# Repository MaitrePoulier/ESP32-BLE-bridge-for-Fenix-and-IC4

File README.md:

# ESP32 BaseBoard - IC4 Bridge

**IC4 Bridge** turns the ESP32 BaseBoard into a Bluetooth bridge for indoor cycling. A Garmin Fenix 8 no longer
connects to the Schwinn IC4 bike (Garmin bug in FTMS "Trainer" mode). The bridge connects to the bike instead and
sends its data again as a standard **cycling power sensor** that the watch accepts: power, cadence, speed and
distance. It also reads the heart rate of a **Garmin HRM 600** strap.

On its 4" screen, next to the bike:

* at the top, the state of each link (IC4, Fenix, HRM 600) with a coloured dot, and the time of day;
* on the left, the heart rate in a gauge coloured by heart rate zone, with the current zone below;
* in the centre, the power (W) and the distance of the session (km);
* on the right, the cadence in a gauge coloured by cadence zone (green: target cadence).

Touching the screen shows a diagnostic page for the IC4 link.

## BaseBoard

* 2x 18650 LiFePo4 cells that can be charged with the USB connector: more than 5 h of use as an IC4 Bridge
* Low noise +/- 12.4 V going to the mezzanine to power the audio op-amps
* I2S port going to the mezzanine
* MHS 4.0" screen (ST7796S, 480 x 320) with touch (XPT2046)
* Fits inside a Pelican 1040 Micro Case

The IC4 Bridge uses no mezzanine (no audio): the +/- 12.4 V and the I2S port are unused.

The board is easy to order assembled from JLCPCB: the LCSC part numbers are in the schematic, and the production
files (Gerber, BOM, CPL) are in `Hardware/jlcpcb/production_files/` (JLCPCB Tools plugin for KiCad).

Folders: `Hardware/` (KiCad), `Enclosure/` (3D models of the case), `Datasheets/`, `Design/` (pictures of the
README, design notes), `Firmware/`.

## Firmware

ESP-IDF v6.1 project (ESP32-WROOM-32E-N8R2), NimBLE, LVGL 9 for the GUI.

```bash
cd Firmware
idf.py set-target esp32      # only the first time
idf.py build
idf.py -p /dev/ttyUSB0 flash monitor
```

* `main/` : application sources, `main/include/` : headers
* `main/include/Config.h` : pins of the board (screen, touch, I2S, battery), bridge constants, heart rate and
  cadence zones
* `sdkconfig.defaults` : project configuration (PSRAM, flash 8 MB, LVGL and its fonts, NimBLE, watchdog, core dump)
* `main/idf_component.yml` : external components (LVGL), downloaded in `managed_components/`

Serial console (115200 bauds, ANSI terminal such as Tera Term or `idf.py monitor`; opening the port resets the
board): type `help`.

* `bridge` (status of the links, last FTMS frame decoded, data sent), `bridge raw [off]` (every frame),
  `bridge log [clear]` (event log), `bridge unpair` (erase the bonds kept by the bridge)
* `hrm` (strap, battery, heart rate), `hrm forget` (forget the saved strap)
* `wifi list|scan|connect|forget` (networks used for the time of day), `touch cal|test`, `ui perf|benchmark`,
  `restart`

After a crash (event log: "Boot N (PANIC)"), the core dump kept in flash is read with `idf.py coredump-info`.

### Host tests

The FTMS decoder and the crank / wheel data synthesis are plain C, tested on the PC:

```bash
cd Firmware
gcc -std=c11 -Wall -Wextra -Imain/include test/host/test_bridge.c main/Ftms.c main/Crank.c -lm -o /tmp/test_bridge
/tmp/test_bridge
```

## IC4 Bridge

```
 Schwinn IC4 "IC Bike"            ESP32 "IC4 Bridge"                      Fenix 8
 FTMS 0x1826           notify     central: Ic4Client.c     peripheral:    Sensors > Add > Power
 Indoor Bike Data 0x2AD2 ------>  Ftms.c (decoder)         BleServer.c --> Cycling Power 0x1818
                                  Crank.c (crank and       1 Hz           Cycling Speed and Cadence 0x1816
                                  wheel data)                             Device Information 0x180A

 Garmin HRM 600                                                           any client
 Heart Rate 0x180D     notify     central: HrmClient.c     peripheral:
 HR Measurement 0x2A37 ------>    BridgeScreen.cpp         BleServer.c --> Heart Rate 0x180D (each value)
```

### Use

1. The first time, hold the Bluetooth button of the IC4 for 3 s so that the bridge can pair with it. Afterwards,
   the bridge finds the IC4 as soon as the bike wakes up (pedalling), and the HRM 600 as soon as it is worn.
2. On the Fenix, add the bridge **only as a power sensor**: Sensors > Add > Power > IC4 Bridge. Power, cadence,
   speed and distance then come from this one sensor. If the speed is wrong, set the wheel size of the sensor to
   2096 mm (Manual).
3. HRM 600: put it in its **open** connection type once (press its button twice quickly; LED: three green flashes
   every 5 s). The first strap named "HRM 600" / "HRM600" is saved; `hrm forget` to change.
4. IC4 console: do not pair "IC4 Bridge" as its heart rate sensor (see below).
5. Time of day (optional): save a WiFi network in the serial console with `wifi connect <ssid> [password]`. At each
   boot the bridge gets the time over WiFi (SNTP), then turns the WiFi off.

### Fenix side (peripheral)

* Cycling Power Measurement (0x2A63, 1 Hz): flags 0x0030, power (sint16), cumulative wheel revolutions (uint32),
  last wheel event time (uint16, 1/2048 s), cumulative crank revolutions (uint16), last crank event time (uint16,
  1/1024 s). The crank data are synthesised by integrating the FTMS cadence, the wheel data by integrating the FTMS
  speed with a 2096 mm wheel (`WHEEL_CIRCUMFERENCE_MM`); cadence 0 or no FTMS data for more than 3 s: power 0 and
  crank / wheel data frozen.
* The same wheel data are also sent by a speed sensor (Cycling Speed and Cadence 0x1816, CSC Measurement 0x2A5B,
  wheel only). The Fenix does not need it: it takes speed and distance from the power sensor.
* Control points (0x2A66 power, 0x2A55 speed): Set Cumulative Value (wheel revolutions) and, for the power,
  Start Offset Compensation (the "calibration" proposed by the watch, answered with an offset of 0).
* Heart Rate service (0x180D): each value received from the HRM 600 is notified at once (uint8, body location
  chest); no heart rate for 5 s: nothing is sent any more.
* Advertising data: only Cycling Power (0x1818); Heart Rate (0x180D) and CSC (0x1816) are in the scan response.
  With 0x180D in the advertising data, the Fenix classified the bridge as a heart rate strap: it did not appear in
  the "Power" search and, added from "all sensors", it subscribed only to the heart rate.
* One public address for both roles: a random static address for the central role made the ESP32 controller
  advertise with it too, and the Fenix saw an unknown second bridge.
* Up to 3 clients. A repeated pairing that fails (Fenix: DHKey check error) is fixed by removing the sensor on the
  watch and `bridge unpair` on the bridge.

### IC4 and HRM 600 side (central)

* Everything BLE runs in the NimBLE host task (GAP/GATT callbacks and `ble_npl_callout` timers): a reconnection
  never blocks the server.
* The bridge never writes the Fitness Machine Control Point (0x2AD9) and never reads the IC4 heart rate service.
* IC4: reconnection with a backoff of 1 s, 2 s, 4 s... 30 s max; a connection without data for 15 s is closed and
  restarted. Its address is saved in NVS.
* HRM 600: the first strap whose name starts with "HRM 600" or "HRM600" (`HRM_NAME_PREFIXES`) and advertising
  0x180D is used, and its address is saved in NVS: from then on only this strap. The IC4, the bridges and the
  watches broadcasting the heart rate are excluded. In its secure connection type the strap requires an
  authenticated link, impossible without screen or keyboard: the screen then shows "Secure mode: press its button
  2x". Its battery level is read at each connection.
* The IC4 and HRM clients take turns to scan and connect (one scan or connection establishment at a time).
* IC4 console: the bike and its console are one chip with one address, and only one link per peer is possible.
  Over a link opened by the console (to get the bridge heart rate), the IC4 sends no Indoor Bike Data (checked
  2026-11-21: 0 frames in 15 s, although the subscription succeeds). The bridge therefore closes such a link at once
  and connects itself: the IC4 console cannot show the heart rate, which is shown on the bridge screen.
* The IC4 does not send its resistance level over BLE (FTMS features 0x00000000).

### Screen

* Garmin style, refreshed 30 times per second.
* Top: IC4, Fenix and HRM 600 with a dot (green: data, orange: waiting, red: not found) and their state, time of day
  (SNTP over WiFi at boot, then the WiFi driver is released; empty until the time is known).
* Gauges: 270 degree arcs made of 5 coloured bands, each as wide as its span of values, and a marker in the colour
  of the current zone. Zones in `Config.h`, same colours for both gauges (grey, blue, green, orange, red):
  * heart rate: Z1 92, Z2 118, Z3 133, Z4 156, Z5 166-183 bpm (zone shown below the gauge);
  * cadence: Z1 50, Z2 60, Z3 80 (target, green), Z4 95, Z5 105-120 rpm.
* Centre: power (W) and distance of the session (km, integrated from the IC4 speed, back to 0 after 10 min without
  pedalling).
* Touching the screen shows the IC4 details page (last raw frame and its decoding, FTMS characteristics, devices
  seen while scanning, latest events): the diagnostic is possible next to the bike, without the console. Touch again
  to come back.

### Reliability

* Event log kept in flash across restarts: boots (with the reset reason), connections, disconnections, devices
  seen, first FTMS frames of each connection (`bridge log`).
* Task watchdog: the board restarts if the LVGL loop or an idle task stops for 10 s.
* Core dump to the `coredump` partition after a crash.

### Status

* Checked on the bike: Fenix 8 as a power sensor (power, cadence, speed, distance), HRM 600 heart rate on the
  screen.
* Not possible: heart rate on the IC4 console (see above).
* Idea: estimate the resistance level from power and cadence, with a calibration session.
* Unknown: how many simultaneous BLE connections the HRM 600 accepts.

## License

* Firmware (`Firmware/`) and documentation: [GNU GPL v3](LICENSE).
* Hardware (`Hardware/`, KiCad) and enclosure (`Enclosure/`): [CERN-OHL-S v2](Hardware/LICENSE), strongly
  reciprocal: modified designs must stay open under the same licence.

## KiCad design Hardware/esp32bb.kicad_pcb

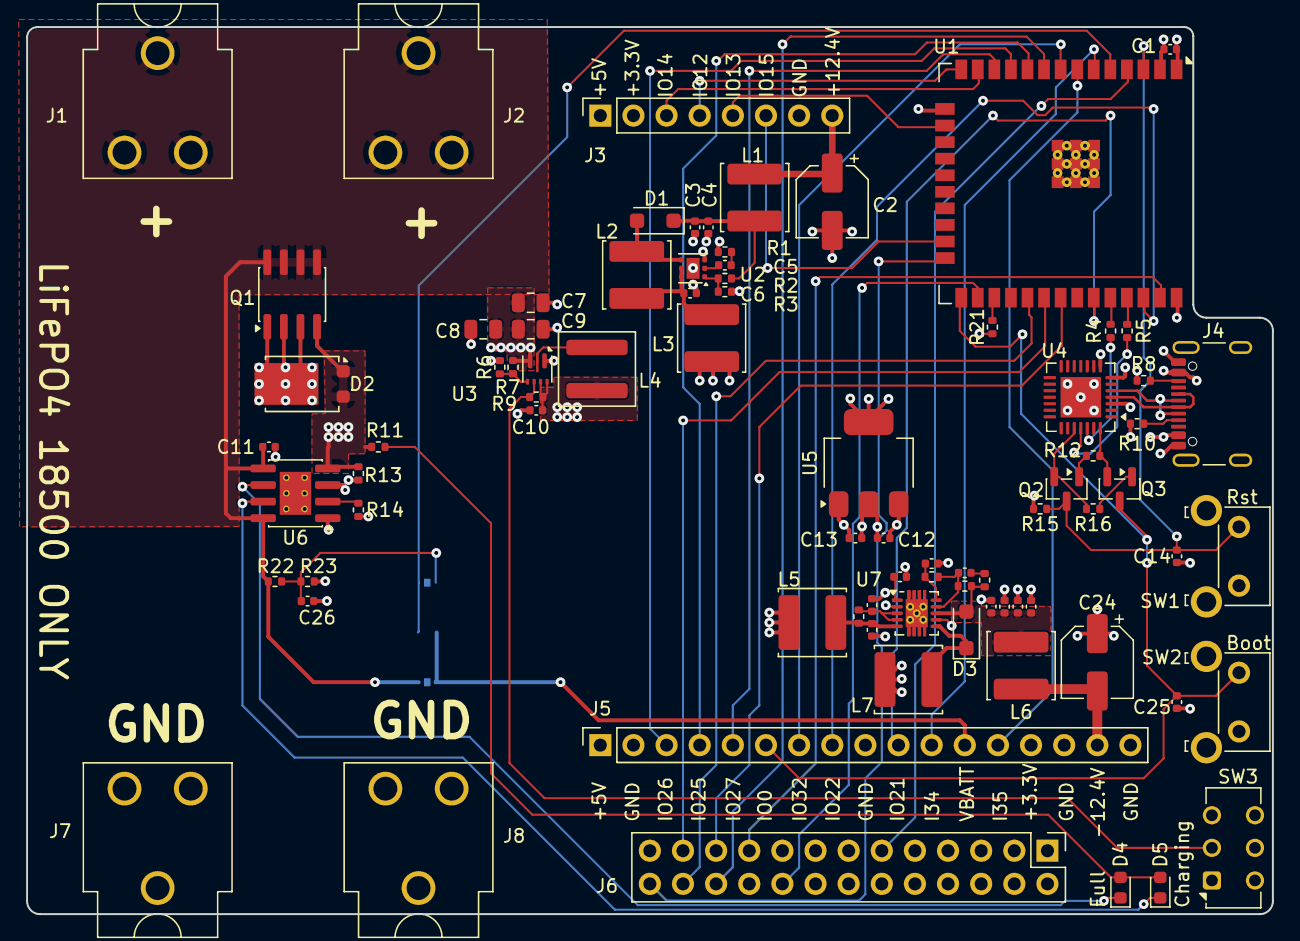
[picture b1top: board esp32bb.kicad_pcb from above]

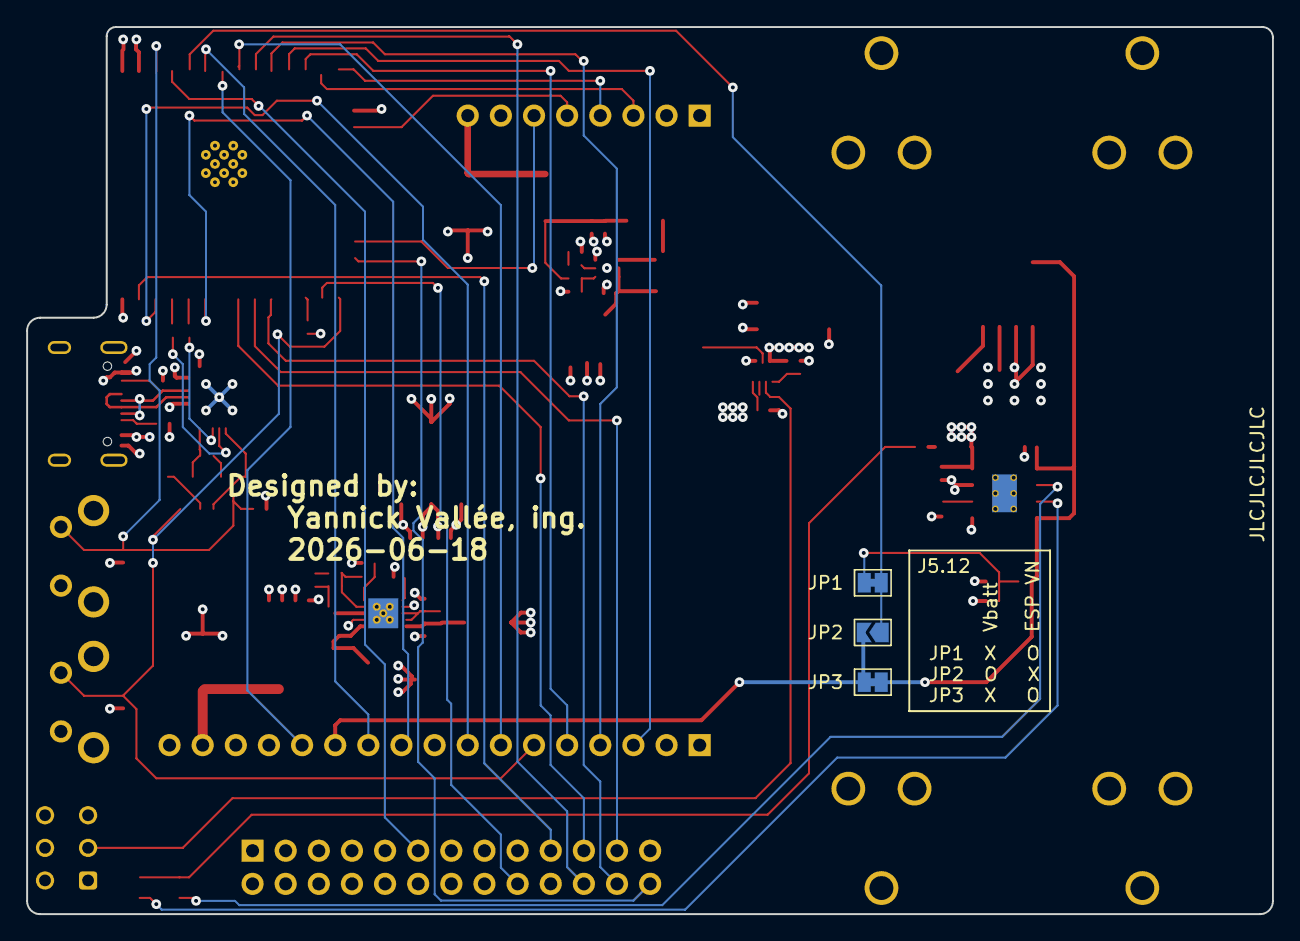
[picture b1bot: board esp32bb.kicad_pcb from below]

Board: 4 copper layers, 95.5 x 68.0 mm, 85 parts (3 on the bottom side), 67 nets.

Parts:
C1, C6, C10, C11, C12, C13, C23: 10uF; C_0402_1005Metric
C2, C24: 22uF; CP_Elec_5x5.9
C3, C19, C20, C21, C22: 4.7uF; C_0402_1005Metric
C4, C5, C17, C26: 4.7nF; C_0402_1005Metric
C7, C8, C9: 22uF; C_0805_2012Metric
C14, C25: 1nF; C_0402_1005Metric
C15, C18: 220nF; C_0402_1005Metric
C16: 10pF; C_0402_1005Metric
D1, D3: D_Schottky; D_SOD-123F
D2: Fuxinsemi_PDS760; TO-277B
D4: Green, 3.2V; LED_0603_1608Metric
D5: Blue 2.9V; LED_0603_1608Metric
J1, J2, J7, J8: Conn_01x01_Socket; BatteryClip_Keystone_54_D16-19mm
J3: Conn_01x08; PinSocket_1x08_P2.54mm_Vertical
J4: USB_C_Receptacle_USB2.0_16P; USB_C_Receptacle_GCT_USB4105-xx-A_16P_TopMnt_Horizontal
J5: PM254-1-17-Z-8.5; PinSocket_1x17_P2.54mm_Vertical
J6: Conn_02x13_Odd_Even; PinHeader_2x13_P2.54mm_Vertical
JP1, JP3: SolderJumper_2_Bridged; SolderJumper-2_P1.3mm_Bridged_Pad1.0x1.5mm
JP2: SolderJumper_2_Open; SolderJumper-2_P1.3mm_Open_TrianglePad1.0x1.5mm
L1, L3, L5, L6: 2.9Ohms @ 1Mhz; L_Chilisin_BWVS00505030
L2, L7: 10uH; L_Chilisin_BWVS00505030
L4: 1uH; L_Coilcraft_XAL5030-XXX
Q1: DMP3015LSS-13; SOIC-8_3.9x4.9mm_P1.27mm
Q2, Q3: MMBT3904; SOT-23
R1, R3, R12, R15, R16, R21: 10k; R_0402_1005Metric
R2: 91k; R_0402_1005Metric
R4, R5: 100; R_0402_1005Metric
R6, R9, R13, R18: 100k; R_0402_1005Metric
R7, R22, R23: 732k; R_0402_1005Metric
R8, R10: 5.1k; R_0402_1005Metric
R11: 180; R_0402_1005Metric
R14: 1.18k; R_0402_1005Metric
R17: 150k; R_0402_1005Metric
R19: 1.54M; R_0402_1005Metric
R20: 10Ω; R_0402_1005Metric
SW1, SW2: SW_Push; SW_SPST_Omron_B3F-315x_Angled
SW3: SW_Push_DPDT; SW_CK_JS202011AQN_DPDT_Angled
U1: ESP32-WROOM-32E-N8R2; ESP32-WROOM-32E-0p3mm
U2: TPS61170DRVR; WSON-6-1EP_2x2mm_P0.65mm_EP1x1.6mm
U3: TPS61022; Texas_RWU0007A_VQFN-7_2x2mm_P0.5mm
U4: CP2102; QFN-28-1EP_5x5mm_P0.5mm_EP3.1x3.1mm
U5: LT1963AEST-3.3#TRPBF; SOT-223-3_TabPin2
U6: CN3158; SOIC-8-1EP_3.9x4.9mm_P1.27mm_EP2.41x3.3mm_ThermalVias-0p3mm
U7: TPS63700; Texas_S-PWSON-N10_ThermalVias

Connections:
+3.3V: C1.1, C12.1, J3.2, J5.14, J6.1, J6.17, R15.2, R21.1, U1.2 (3V3), U5.3 (OUT)
+5V: C7.1, C8.1, C9.1, C13.1, J3.1, J5.1, J6.2, J6.4, L3.1, L5.1, R7.2, U3.3 (VOUT), U4.7 (REGIN), U4.8 (VBUS), U5.1 (IN)
+12.4V: C2.1, J3.8, L1.2
-12.4V: C24.2, J5.16, L6.2
/Power/Vin: C10.1, D2.3 (K), L4.1, Q1.1 (S), Q1.2 (S), Q1.3 (S), R9.1, U3.6 (MODE), U3.7 (VIN)
Batt-Monitor: JP1.2 (B), JP2.1 (A), U1.5 (SENSOR_VN)
D+: J4.A6 (D+), J4.B6 (D+), U4.4 (D+)
D-: J4.A7 (D-), J4.B7 (D-), U4.5 (D-)
DTR: Q3.2 (E), R12.2, U4.28 (DTR)
EN: C14.1, Q2.3 (C), R15.1, SW1.1, U1.3 (EN)
GND: C1.2, C2.2, C3.2, C4.2, C6.2, C7.2, C8.2, C9.2, C10.2, C11.2, C12.2, C13.2, C14.2, C15.1, C17.2, C18.1, C19.2, C20.2, C21.2, C22.2, C23.2, C24.1, C25.2, C26.2, J3.7, J4.A1 (GND), J4.A12 (GND), J4.B1 (GND), J4.B12 (GND), J4.SH (SHIELD), J5.2, J5.9, J5.15, J5.17, J6.6, J6.9, J6.14, J6.20, J6.25, J7.1 (Pin_1_1), J8.1 (Pin_1_1), L7.1, R1.1, R3.1, R6.1, R8.2, R10.2, R13.2, R14.1, R23.1, SW1.2, SW2.2, SW3.3 (C), U1.1 (GND), U1.15 (GND), U1.38 (GND), U1.39 (GND-PAD), U2.3 (GND), U2.7 (TP), U3.1 (GND), U4.3 (GND), U4.29 (GND), U5.2 (GND), U6.1 (TEMP), U6.3 (GND), U6.9 (GND), U7.2 (GND), U7.7 (PS_GND), U7.11 (TP)
I34: J5.11, U1.6 (IO34)
I35: J5.13, U1.7 (IO35)
IO0(boot): C25.1, J5.6, Q3.3 (C), SW2.1, U1.25 (IO0)
IO12: J3.4, U1.14 (IO12)
IO13: J3.5, U1.16 (IO13)
IO14: J3.3, U1.13 (IO14)
IO15: J3.6, U1.23 (IO15)
IO21: J5.10, U1.33 (IO21)
IO22: J5.8, U1.36 (IO22)
IO25: J5.4, U1.10 (IO25)
IO26: J5.3, U1.11 (IO26)
IO27: J5.5, U1.12 (IO27)
IO32: J5.7, U1.8 (IO32)
LCD_CS: J6.24, U1.29 (IO5)
LCD_RS: J6.18, U1.26 (IO4)
LCD_RST: J6.22, U1.9 (IO33)
LCD/TP_CLK: J6.23, U1.30 (IO18)
LCD/TP_MISO: J6.21, U1.31 (IO19)
LCD/TP_MOSI: J6.19, U1.37 (IO23)
unnamed: C5.2, R1.2
unnamed: C16.2, R18.2
unnamed: D1.2 (A), L2.2, U2.4 (SW)
unnamed: C3.1, C4.1, D1.1 (K), L1.1, R2.2
unnamed: C19.1, C20.1, C21.1, C22.1, D3.2 (A), L6.1, R18.1, R19.1, U7.8 (OUT)
unnamed: D3.1 (K), L7.2, U7.6 (SW)
unnamed: D4.2 (A), D5.2 (A), R11.1
unnamed: D4.1 (K), U6.6 (~DONE)
unnamed: D5.1 (K), U6.7 (~CHRG)
unnamed: J4.A5 (CC1), R10.1
unnamed: J4.B5 (CC2), R8.1
unnamed: C26.1, JP1.1 (A), R22.1, R23.2
unnamed: Q2.1 (B), R12.1
unnamed: Q3.1 (B), R16.1
unnamed: R21.2, U1.27 (IO16)
unnamed: C5.1, U2.2 (COMP)
unnamed: C6.1, L2.1, L3.2, U2.5 (CTRL), U2.6 (VIN)
unnamed: R2.1, R3.2, U2.1 (FB)
unnamed: R9.2, SW3.2 (B), U3.5 (EN)
unnamed: R6.2, R7.1, U3.4 (FB)
unnamed: L4.2, U3.2 (SW)
unnamed: R5.1, U4.25 (RXD)
unnamed: R4.1, U4.26 (TXD)
unnamed: R14.2, U6.2 (ISET)
unnamed: C17.1, U7.1 (COMP)
unnamed: C18.2, R20.1, U7.3 (VIN), U7.4 (EN)
unnamed: C16.1, R17.1, R19.2, U7.9 (FB)
unnamed: C23.1, L5.2, R20.2, U7.5 (IN)
unnamed: C15.2, R17.2, U7.10 (VREF)
RTS: Q2.2 (E), R16.2, U4.24 (RTS)
RXDtoTXD0: R5.2, U1.35 (TXD0)
TP_CS: J6.26, U1.24 (IO2)
TP_IRQ: J6.11, U1.4 (SENSOR_VP)
TXDtoRXD0: R4.2, U1.34 (RXD0)
V-USB: D2.1 (A), D2.2 (A), J4.A4 (VBUS), J4.A9 (VBUS), J4.B4 (VBUS), J4.B9 (VBUS), Q1.4 (G), R11.2, R13.1, U6.4 (VIN)
Vbatt: C11.1, J1.1 (Pin_1_1), J2.1 (Pin_1_1), JP3.1 (A), Q1.5 (D), Q1.6 (D), Q1.7 (D), Q1.8 (D), R22.2, U6.5 (BAT), U6.8 (FB)
Vbatt-VN: J5.12, JP2.2 (B), JP3.2 (B)
